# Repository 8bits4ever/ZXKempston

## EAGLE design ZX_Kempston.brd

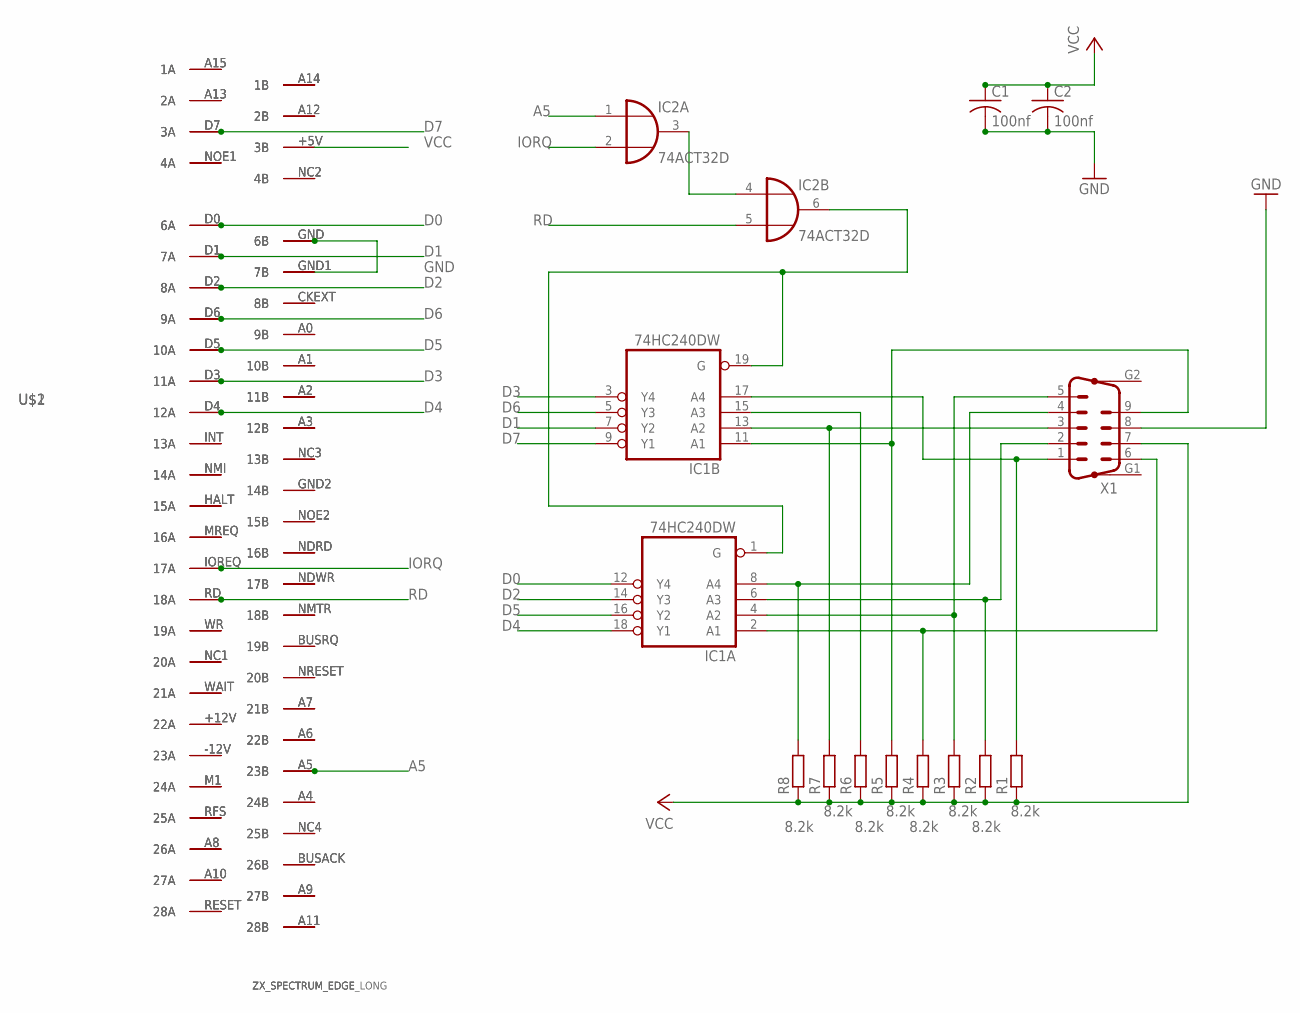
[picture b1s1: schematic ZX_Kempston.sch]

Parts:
C1, C2: 100nf; C0805
IC1: 74HC240DW; SO20W
IC2: 74ACT32D; SO14
R1, R2, R3, R4, R5, R6, R7, R8: 8.2k; M0805
U$1: ZX_SPECTRUM_EDGE; 2X28_EDGE_2.54
U$2: ZX_SPECTRUM_EDGE_LONG; 2X28_EDGE_LONG
X1: M09VP

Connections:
A5: IC2.1 (I0), U$1.A5 (23B), U$2.A5 (23B)
D0: IC1.12 (Y4), U$1.D0 (6A), U$2.D0 (6A)
D1: IC1.7 (Y2), U$1.D1 (7A), U$2.D1 (7A)
D2: IC1.14 (Y3), U$1.D2 (8A), U$2.D2 (8A)
D3: IC1.3 (Y4), U$1.D3 (11A), U$2.D3 (11A)
D4: IC1.18 (Y1), U$1.D4 (12A), U$2.D4 (12A)
D5: IC1.16 (Y2), U$1.D5 (10A), U$2.D5 (10A)
D6: IC1.5 (Y3), U$1.D6 (9A), U$2.D6 (9A)
D7: IC1.9 (Y1), U$1.D7 (3A), U$2.D7 (3A)
GND: C1.2, C2.2, IC1.10 (GND), IC2.7 (GND), U$1.GND (6B), U$1.GND1 (7B), U$2.GND (6B), U$2.GND1 (7B), X1.8
IORQ: IC2.2 (I1), U$1.IOREQ (17A), U$2.IOREQ (17A)
unnamed: U$1.RESET (28A), U$2.RESET (28A)
unnamed: U$1.A9 (27B), U$2.A9 (27B)
unnamed: U$1.A10 (27A), U$2.A10 (27A)
unnamed: U$1.BUSACK (26B), U$2.BUSACK (26B)
unnamed: U$1.A8 (26A), U$2.A8 (26A)
unnamed: U$1.NC4 (25B), U$2.NC4 (25B)
unnamed: U$1.RFS (25A), U$2.RFS (25A)
unnamed: U$1.A4 (24B), U$2.A4 (24B)
unnamed: U$1.M1 (24A), U$2.M1 (24A)
unnamed: U$1.-12V (23A), U$2.-12V (23A)
unnamed: U$1.A6 (22B), U$2.A6 (22B)
unnamed: U$1.+12V (22A), U$2.+12V (22A)
unnamed: U$1.A7 (21B), U$2.A7 (21B)
unnamed: U$1.WAIT (21A), U$2.WAIT (21A)
unnamed: U$1.NRESET (20B), U$2.NRESET (20B)
unnamed: U$1.NC1 (20A), U$2.NC1 (20A)
unnamed: U$1.BUSRQ (19B), U$2.BUSRQ (19B)
unnamed: U$1.WR (19A), U$2.WR (19A)
unnamed: U$1.NMTR (18B), U$2.NMTR (18B)
unnamed: U$1.NDWR (17B), U$2.NDWR (17B)
unnamed: U$1.NDRD (16B), U$2.NDRD (16B)
unnamed: U$1.MREQ (16A), U$2.MREQ (16A)
unnamed: U$1.NOE2 (15B), U$2.NOE2 (15B)
unnamed: U$1.HALT (15A), U$2.HALT (15A)
unnamed: U$1.GND2 (14B), U$2.GND2 (14B)
unnamed: U$1.NMI (14A), U$2.NMI (14A)
unnamed: U$1.NC3 (13B), U$2.NC3 (13B)
unnamed: U$1.INT (13A), U$2.INT (13A)
unnamed: U$1.A3 (12B), U$2.A3 (12B)
unnamed: U$1.A2 (11B), U$2.A2 (11B)
unnamed: U$1.A1 (10B), U$2.A1 (10B)
unnamed: U$1.A0 (9B), U$2.A0 (9B)
unnamed: U$1.CKEXT (8B), U$2.CKEXT (8B)
unnamed: U$1.NC2 (4B), U$2.NC2 (4B)
unnamed: U$1.NOE1 (4A), U$2.NOE1 (4A)
unnamed: U$1.A12 (2B), U$2.A12 (2B)
unnamed: U$1.A13 (2A), U$2.A13 (2A)
unnamed: U$1.A14 (1B), U$2.A14 (1B)
unnamed: U$1.A15 (1A), U$2.A15 (1A)
unnamed: U$1.A11 (28B), U$2.A11 (28B)
unnamed: IC1.17 (A4), R1.2, X1.1
unnamed: IC1.6 (A3), R2.2, X1.2
unnamed: IC1.1 (G), IC1.19 (G), IC2.6 (O)
unnamed: IC2.3 (O), IC2.4 (I0)
unnamed: IC1.13 (A2), R7.2, X1.3
unnamed: IC1.8 (A4), R8.2, X1.4
unnamed: IC1.4 (A2), R3.2, X1.5
unnamed: IC1.2 (A1), R4.2, X1.6
unnamed: IC1.15 (A3), R6.2
unnamed: IC1.11 (A1), R5.2, X1.9
RD: IC2.5 (I1), U$1.RD (18A), U$2.RD (18A)
VCC: C1.1, C2.1, IC1.20 (VCC), IC2.14 (VCC), R1.1, R2.1, R3.1, R4.1, R5.1, R6.1, R7.1, R8.1, U$1.+5V (3B), U$2.+5V (3B), X1.7

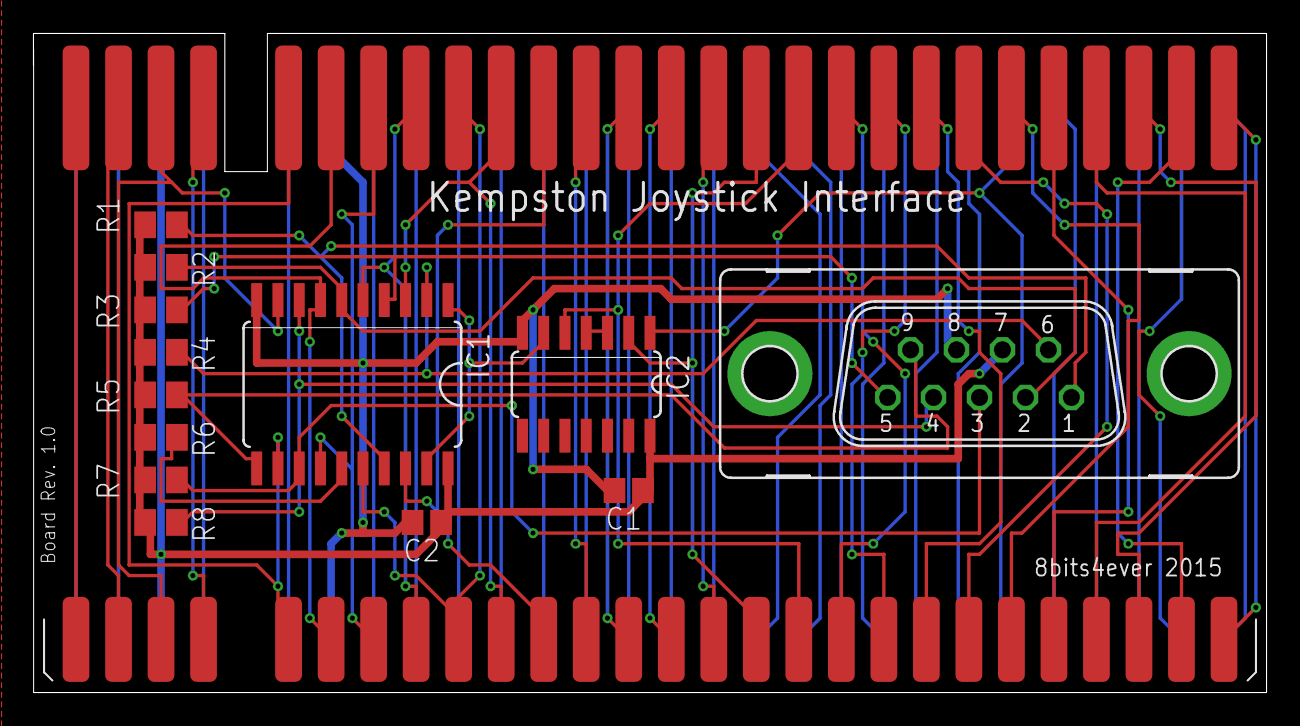
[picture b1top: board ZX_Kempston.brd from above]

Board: 2 copper layers, 73.7 x 39.4 mm, 15 parts (0 on the bottom side), 63 nets.
